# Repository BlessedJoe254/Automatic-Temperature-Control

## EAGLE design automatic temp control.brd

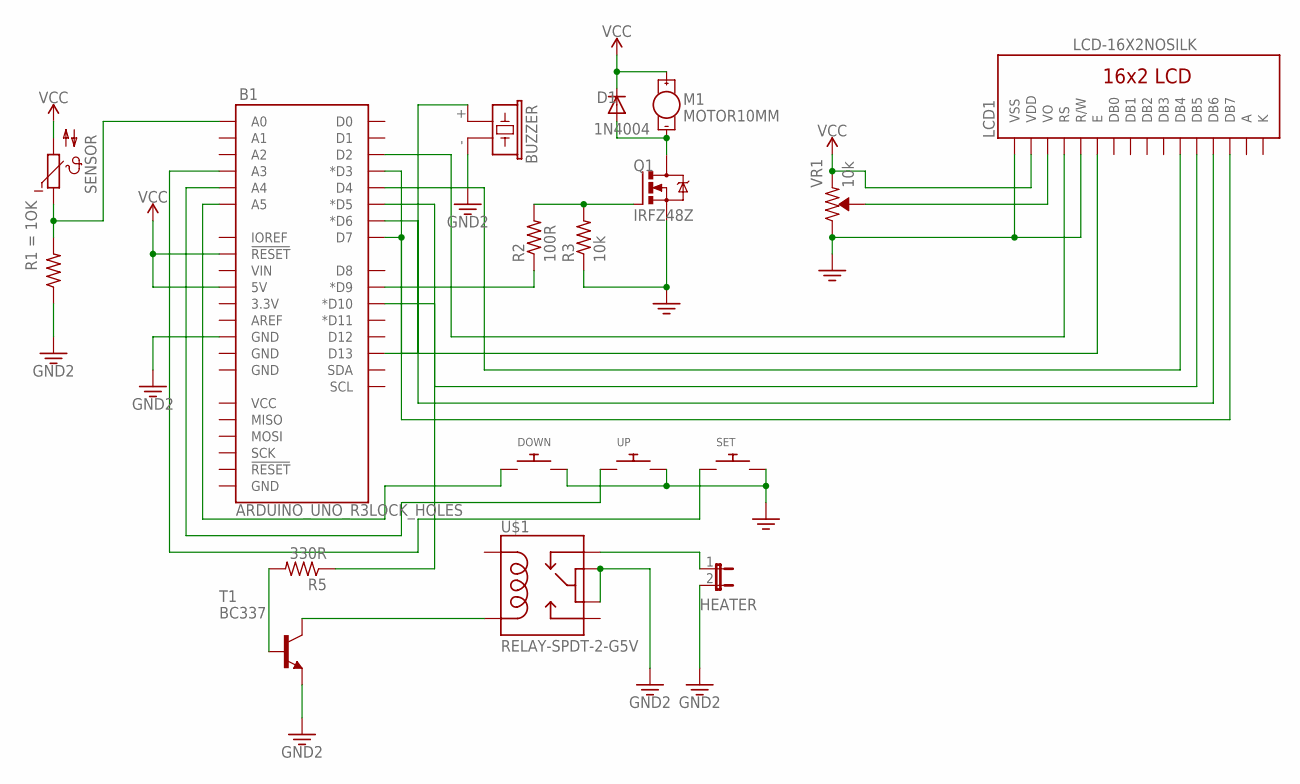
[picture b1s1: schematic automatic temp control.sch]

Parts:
B1: ARDUINO_UNO_R3LOCK_HOLES; ARDUINO_R3_LOCK_HOLES
BUZZER: F/CM04P
D1: 1N4004; DO41-10
DOWN: SWITCH_PUSHBUTTONEVQ-PE; TACT_PANA-EVQ
HEATER: JP1E; JP1
LCD1: LCD-16X2NOSILK; LCD-16X2_NOSILK
M1: MOTOR10MM; VIBE-MOTOR-10MM
Q1: IRFZ48Z; TO220BH
R2: 100R; 0204/7
R3: 10k; 0204/7
R4: R-US_0204/7; 0204/7
R5: 330R; 0204/7
SENSOR: NTC640-9; N640
SET: SWITCH_PUSHBUTTONEVQ-PE; TACT_PANA-EVQ
T1: BC337; TO92
U$1: RELAY-SPDT-2-G5V; RELAY-G5V
UP: SWITCH_PUSHBUTTONEVQ-PE; TACT_PANA-EVQ
VR1: 10k; TRIMPOT-PTH-3386U

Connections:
3.3V: B1.GND@4 (GND), BUZZER.- (2), DOWN.P$2, HEATER.2, LCD1.1 (VSS), LCD1.5 (R/W), Q1.S, R3.1, R4.1, SET.P$2, T1.1 (E), U$1.5, U$1.6, UP.P$2, VR1.3 (CW)
A: LCD1.15 (A)
K: LCD1.16 (K)
unnamed: B1.A0, R4.2, SENSOR.1
unnamed: B1.D10 (*D10), R5.1
unnamed: R5.2, T1.2 (B)
unnamed: T1.3 (C), U$1.9
unnamed: HEATER.1, U$1.1
unnamed: B1.D13, BUZZER.+ (1)
unnamed: B1.D9 (*D9), R2.1
unnamed: Q1.G, R2.2, R3.2
unnamed: D1.A, M1.-, Q1.D
unnamed: B1.A5, DOWN.P$1
unnamed: B1.A4, UP.P$1
unnamed: LCD1.3 (VO), VR1.2 (WIPER)
unnamed: B1.A3, SET.P$1
unnamed: B1.D4, LCD1.11 (DB4)
unnamed: B1.D2, LCD1.4 (RS)
unnamed: B1.D5 (*D5), LCD1.12 (DB5)
unnamed: B1.D6 (*D6), LCD1.13 (DB6)
unnamed: B1.D3 (*D3), B1.D7, LCD1.6 (E), LCD1.14 (DB7)
VCC: B1.5V, B1.RESET@1 (!RESET!), D1.C, LCD1.2 (VDD), M1.+, SENSOR.2, VR1.1 (CCW)

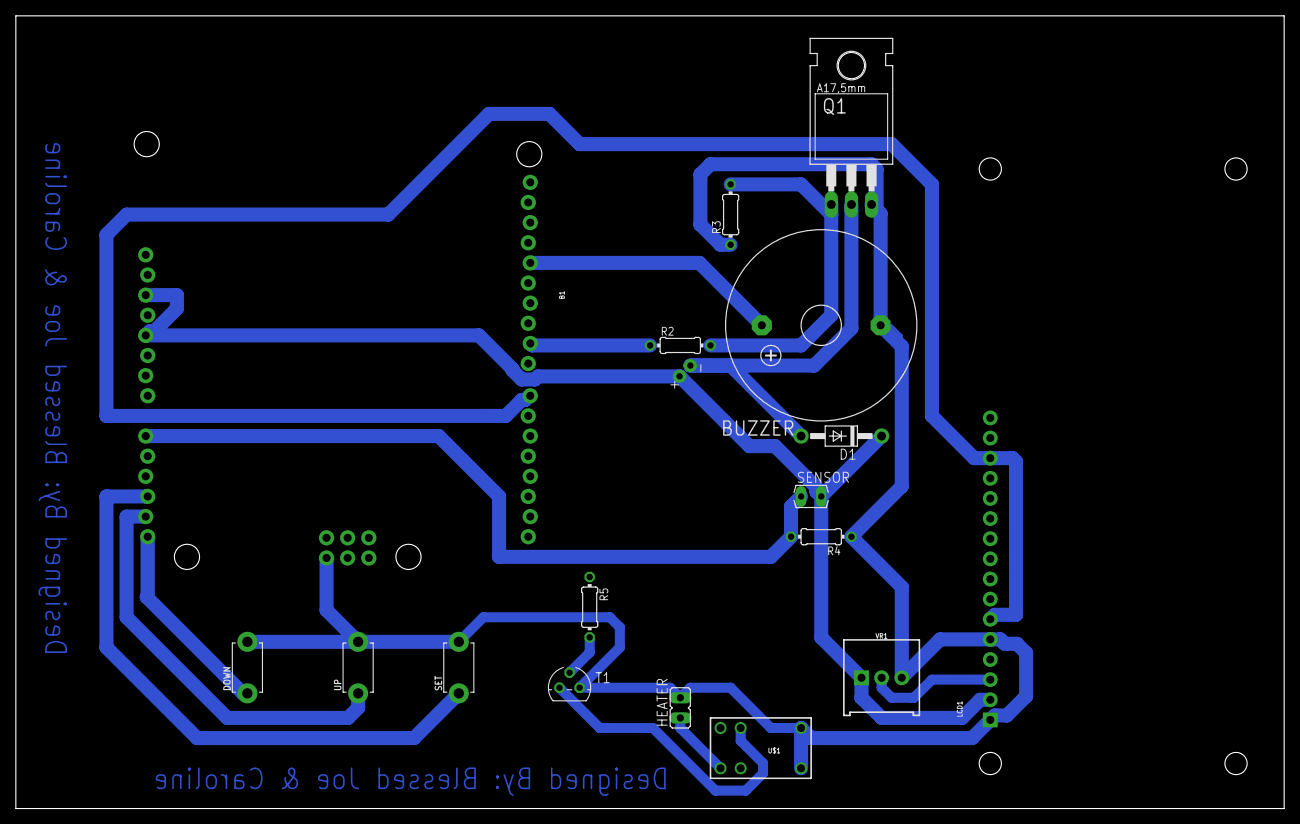
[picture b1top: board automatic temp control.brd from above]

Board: 2 copper layers, 160.0 x 100.0 mm, 18 parts (0 on the bottom side), 20 nets.

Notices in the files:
parts and their libraries:
SparkFun-Boards: Licensing: Creative Commons ShareAlike 4.0 International - https://creativecommons.org/licenses/by-sa/4.0
